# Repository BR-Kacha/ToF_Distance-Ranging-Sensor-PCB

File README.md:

# ToF_Distance-Ranging-Sensor-PCB

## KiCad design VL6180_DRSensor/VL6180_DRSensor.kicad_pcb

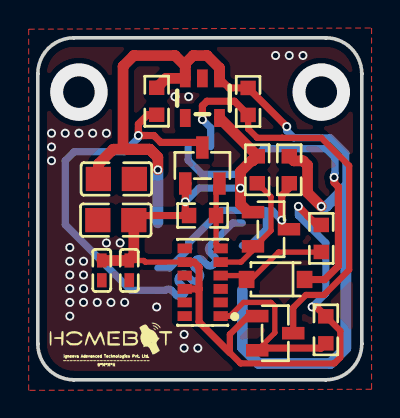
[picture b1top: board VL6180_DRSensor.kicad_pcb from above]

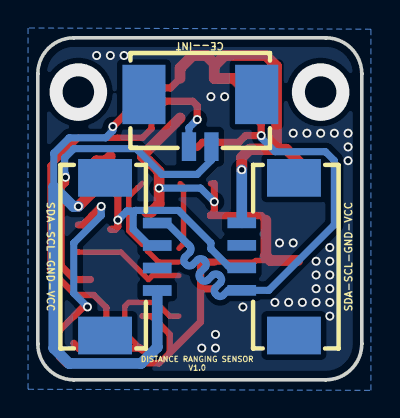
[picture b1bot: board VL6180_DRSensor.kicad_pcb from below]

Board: 2 copper layers, 18.0 x 19.0 mm, 20 parts (3 on the bottom side), 10 nets.

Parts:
C1, C2: CL21A106KAYNNNE; C0805
C3, C4: CL05B104KO5NNNC; C0402
CN4: A1251WR-S-2P; CONN-SMD_A1251WR-S-2P
CN5, CN6: A1251WR-S-4P; CONN-SMD_A1251WR-S-4P
Q1: BL8558-28PRN; SOT-23-5_L2.9-W1.6-P0.95-LS2.8-BL
Q2, Q3, Q4: 2N7002_C916396; SOT-23-3_L2.9-W1.3-P1.90-LS2.4-BR
R1, R2, R3, R4, R5, R6, R7: RC0603FR-074K7L; R0603
U1: 1N5819W_C5451628; SOD-123_L2.7-W1.6-LS3.7-FD
U2: VL6180V1NR/1; LGA-12_L4.8-W2.8-P0.75-BL

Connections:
2.8V: C2.1, C3.1, C4.1, Q1.5 (Vout), Q2.1 (G), Q3.1 (G), Q4.1 (G), R1.1, R5.2, R6.2, R7.1, U2.8 (AVDD_VCSEL), U2.10 (AVDD)
CE: CN4.2, U1.2 (K)
INT: CN4.1, Q4.3 (D), R3.2
INT_2.8V: Q4.2 (S), R7.2, U2.1 (GPIO1)
unnamed: R1.2, U1.1 (A), U2.4 (GPIO0/CE)
SCL: CN5.3, CN6.3, Q3.3 (D), R2.2
SCL_2.8V: Q3.2 (S), R6.1, U2.5 (SCL)
SDA: CN5.4, CN6.4, Q2.3 (D), R4.2
SDA_2.8V: Q2.2 (S), R5.1, U2.6 (SDA)
VCC: C1.1, CN5.1, CN6.1, Q1.1 (Vin), Q1.3 (CE), R2.1, R3.1, R4.1

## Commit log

2025-04-10 Initial Commit
    Snapfit version with 1.25mm JST connecters version added
2025-04-10 Update Verison
    - Screw Hole mounting version with the JST 1.25mm connectors with length tuning
    - Size of the PCB is exact size as available in the market
